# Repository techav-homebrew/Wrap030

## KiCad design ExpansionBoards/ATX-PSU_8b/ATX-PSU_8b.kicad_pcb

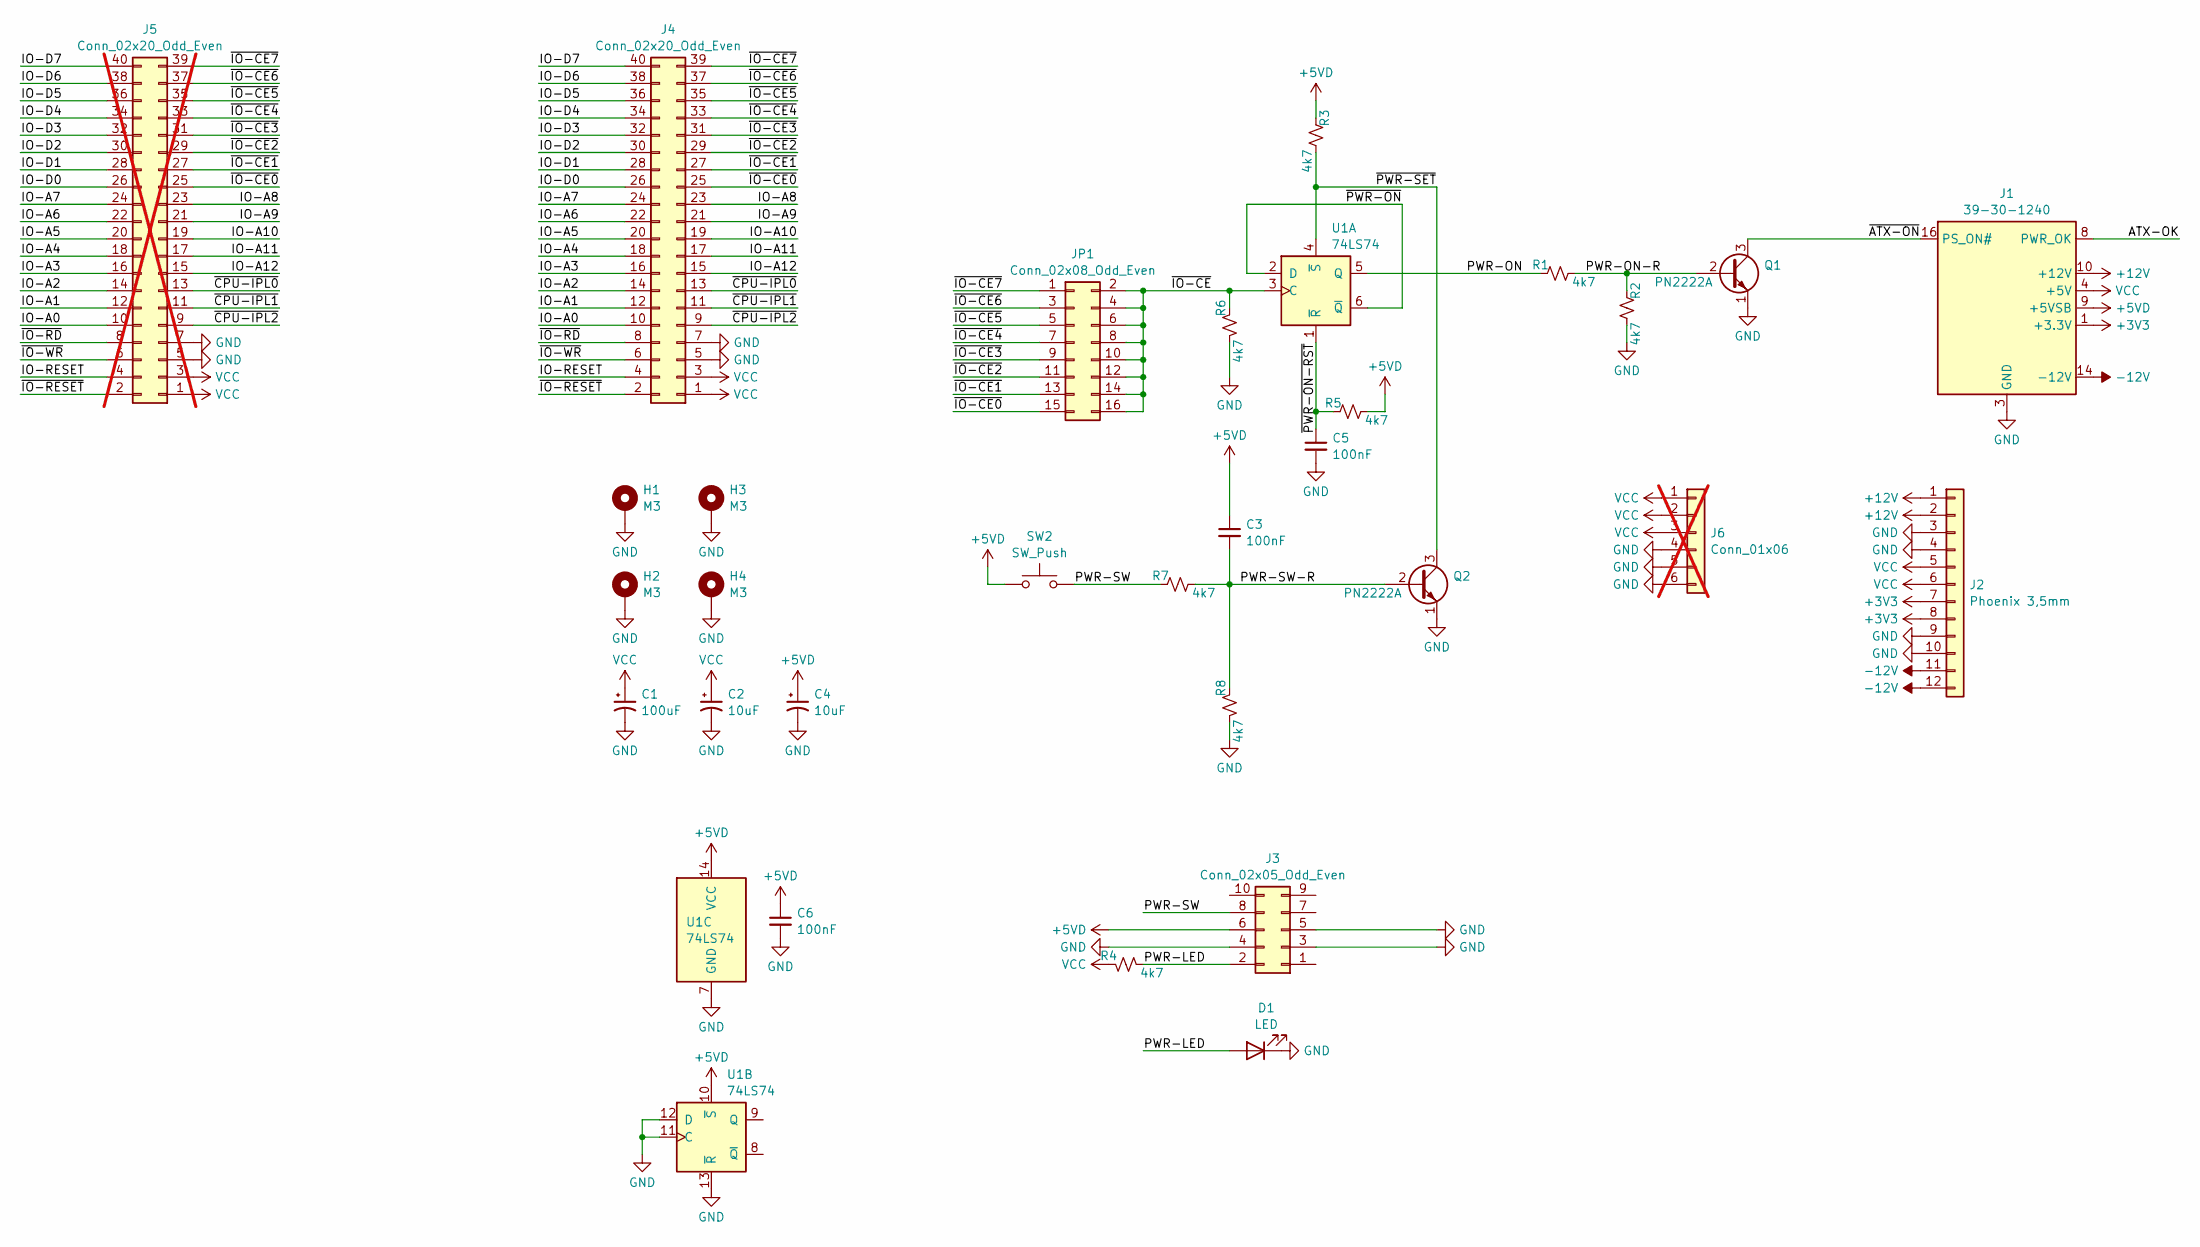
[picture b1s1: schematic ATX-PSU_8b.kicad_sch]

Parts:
C1: 100uF; CP_Radial_D10.0mm_P5.00mm
C2, C4: 10uF; CP_Radial_D5.0mm_P2.50mm
C3, C5, C6: 100nF; C_Disc_D4.3mm_W1.9mm_P5.00mm
D1: LED; LED_D3.0mm
H1, H2, H3, H4: M3; MountingHole_3.2mm_M3_Pad_Via
J1: 39-30-1240; Molex_Mini-Fit_Jr_5569-24A2_2x12_P4.20mm_Horizontal; Mouser 538-39-30-1240
J2: Phoenix 3,5mm; PhoenixContact_MC_1,5_12-G-3.5_1x12_P3.50mm_Horizontal
J3: Conn_02x05_Odd_Even; IDC-Header_2x05_P2.54mm_Vertical
J4: Conn_02x20_Odd_Even; PinHeader_2x20_P2.54mm_Horizontal
J5: Conn_02x20_Odd_Even; PinHeader_2x20_P2.54mm_Vertical; not fitted
J6: Conn_01x06; PinHeader_1x06_P2.54mm_Vertical; not fitted
JP1: Conn_02x08_Odd_Even; PinHeader_2x08_P2.54mm_Vertical
Q1, Q2: PN2222A; TO-92_Inline
R1, R2, R3, R4, R5, R6, R7, R8: 4k7; R_Axial_DIN0204_L3.6mm_D1.6mm_P7.62mm_Horizontal
SW2: SW_Push; SW_PUSH_6mm_H4.3mm
U1: 74LS74; DIP-14_W7.62mm

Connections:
+3V3: J1.1 (+3.3V), J1.2 (+3.3V), J1.12 (+3.3V), J1.13 (+3.3V), J2.7, J2.8
+5VD: C3.1, C4.1, C6.1, J1.9 (+5VSB), J3.6, R3.1, R5.2, SW2.1, U1.10 (~S), U1.14 (VCC)
+12V: J1.10 (+12V), J1.11 (+12V), J2.1, J2.2
-12V: J1.14 (-12V), J2.11, J2.12
/ATX-OK: J1.8 (PWR_OK)
/IO-A0: J4.10, J5.10
/IO-A1: J4.12, J5.12
/IO-A2: J4.14, J5.14
/IO-A3: J4.16, J5.16
/IO-A4: J4.18, J5.18
/IO-A5: J4.20, J5.20
/IO-A6: J4.22, J5.22
/IO-A7: J4.24, J5.24
/IO-A8: J4.23, J5.23
/IO-A9: J4.21, J5.21
/IO-A10: J4.19, J5.19
/IO-A11: J4.17, J5.17
/IO-A12: J4.15, J5.15
/IO-D0: J4.26, J5.26
/IO-D1: J4.28, J5.28
/IO-D2: J4.30, J5.30
/IO-D3: J4.32, J5.32
/IO-D4: J4.34, J5.34
/IO-D5: J4.36, J5.36
/IO-D6: J4.38, J5.38
/IO-D7: J4.40, J5.40
/IO-RESET: J4.4, J5.4
/PWR-LED: D1.2 (A), J3.2, R4.1
/PWR-ON: R1.1, U1.5 (Q)
/PWR-ON-R: Q1.2 (B), R1.2, R2.1
/PWR-SW: J3.8, R7.1, SW2.2
/PWR-SW-R: C3.2, Q2.2 (B), R7.2, R8.1
/~ATX-ON: J1.16 (PS_ON#), Q1.3 (C)
/~CPU-IPL0: J4.13, J5.13
/~CPU-IPL1: J4.11, J5.11
/~CPU-IPL2: J4.9, J5.9
/~IO-CE0: J4.25, J5.25, JP1.15
/~IO-CE1: J4.27, J5.27, JP1.13
/~IO-CE2: J4.29, J5.29, JP1.11
/~IO-CE3: J4.31, J5.31, JP1.9
/~IO-CE4: J4.33, J5.33, JP1.7
/~IO-CE5: J4.35, J5.35, JP1.5
/~IO-CE6: J4.37, J5.37, JP1.3
/~IO-CE7: J4.39, J5.39, JP1.1
/~IO-CE: JP1.2, JP1.4, JP1.6, JP1.8, JP1.10, JP1.12, JP1.14, JP1.16, R6.1, U1.3 (C)
/~IO-RD: J4.8, J5.8
/~IO-RESET: J4.2, J5.2
/~IO-WR: J4.6, J5.6
/~PWR-ON-RST: C5.1, R5.1, U1.1 (~R)
/~PWR-ON: U1.2 (D), U1.6 (~Q)
/~PWR-SET: Q2.3 (C), R3.2, U1.4 (~S)
GND: C1.2, C2.2, C4.2, C5.2, C6.2, D1.1 (K), H1.1, H2.1, H3.1, H4.1, J1.3 (GND), J1.5 (GND), J1.7 (GND), J1.15 (GND), J1.17 (GND), J1.18 (GND), J1.19 (GND), J1.24 (GND), J2.3, J2.4, J2.9, J2.10, J3.3, J3.4, J3.5, J4.5, J4.7, J5.5, J5.7, J6.4, J6.5, J6.6, Q1.1 (E), Q2.1 (E), R2.2, R6.2, R8.2, U1.7 (GND), U1.11 (C), U1.12 (D), U1.13 (~R)
VCC: C1.1, C2.1, J1.4 (+5V), J1.6 (+5V), J1.21 (+5V), J1.22 (+5V), J1.23 (+5V), J2.5, J2.6, J4.1, J4.3, J5.1, J5.3, J6.1, J6.2, J6.3, R4.2

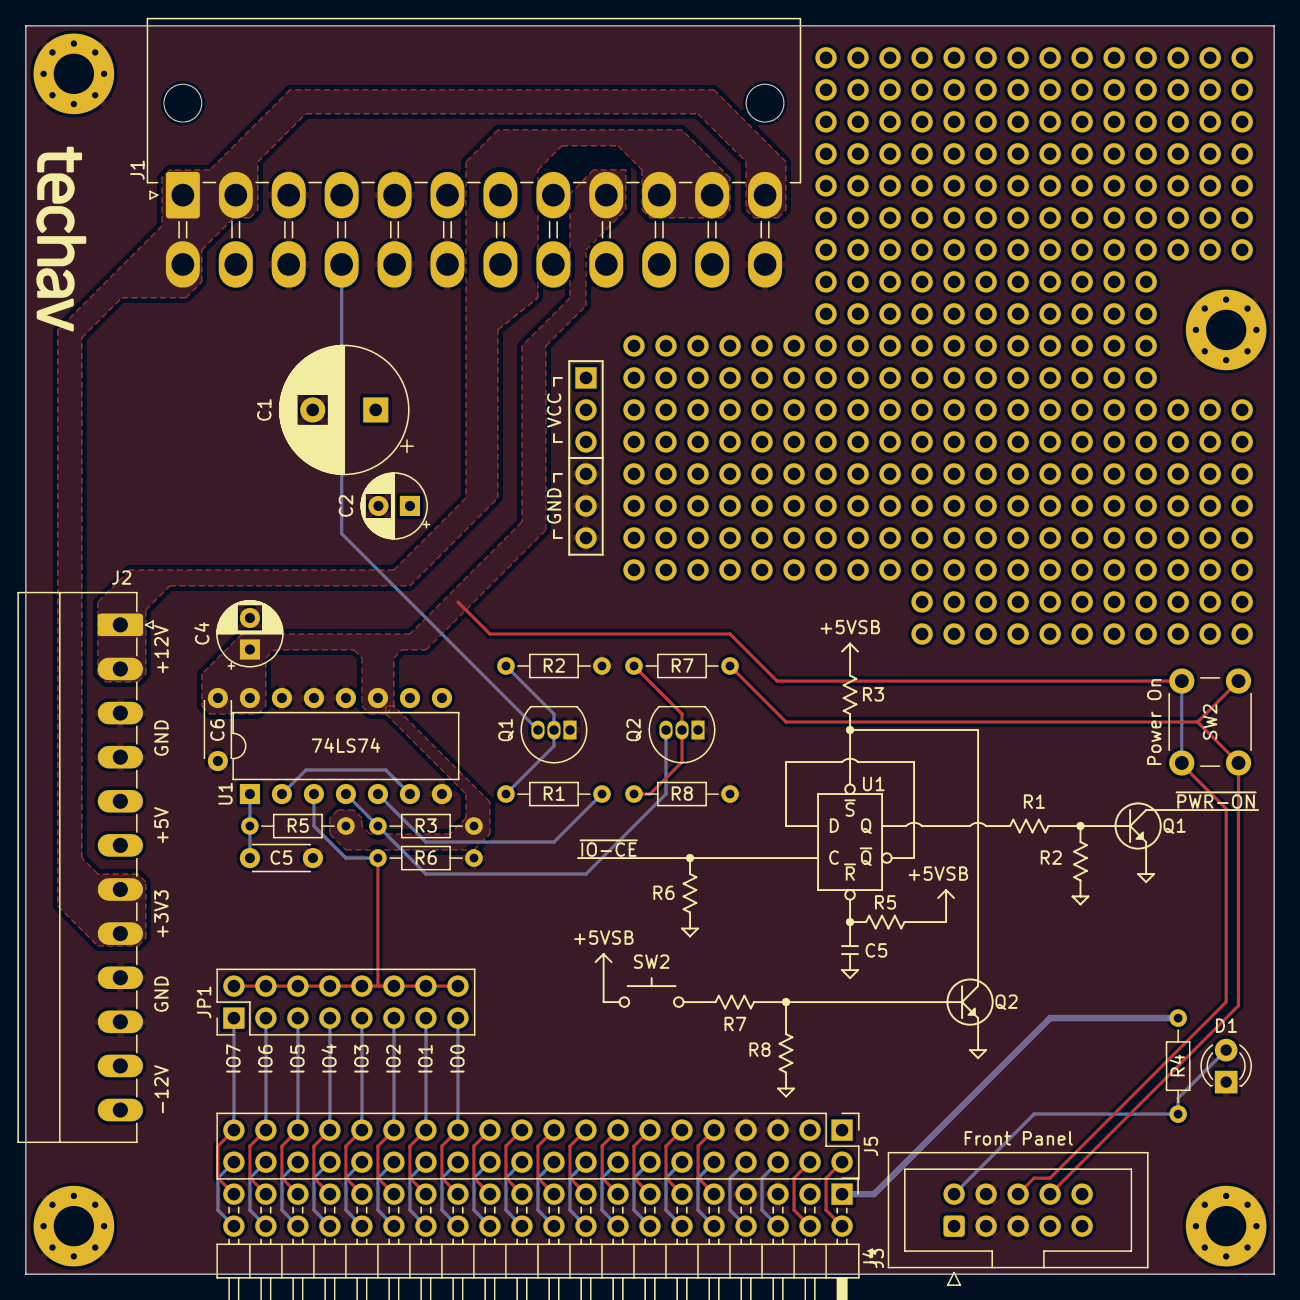
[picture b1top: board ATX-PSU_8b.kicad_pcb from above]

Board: 2 copper layers, 99.1 x 99.1 mm, 29 parts (0 on the bottom side), 52 nets.

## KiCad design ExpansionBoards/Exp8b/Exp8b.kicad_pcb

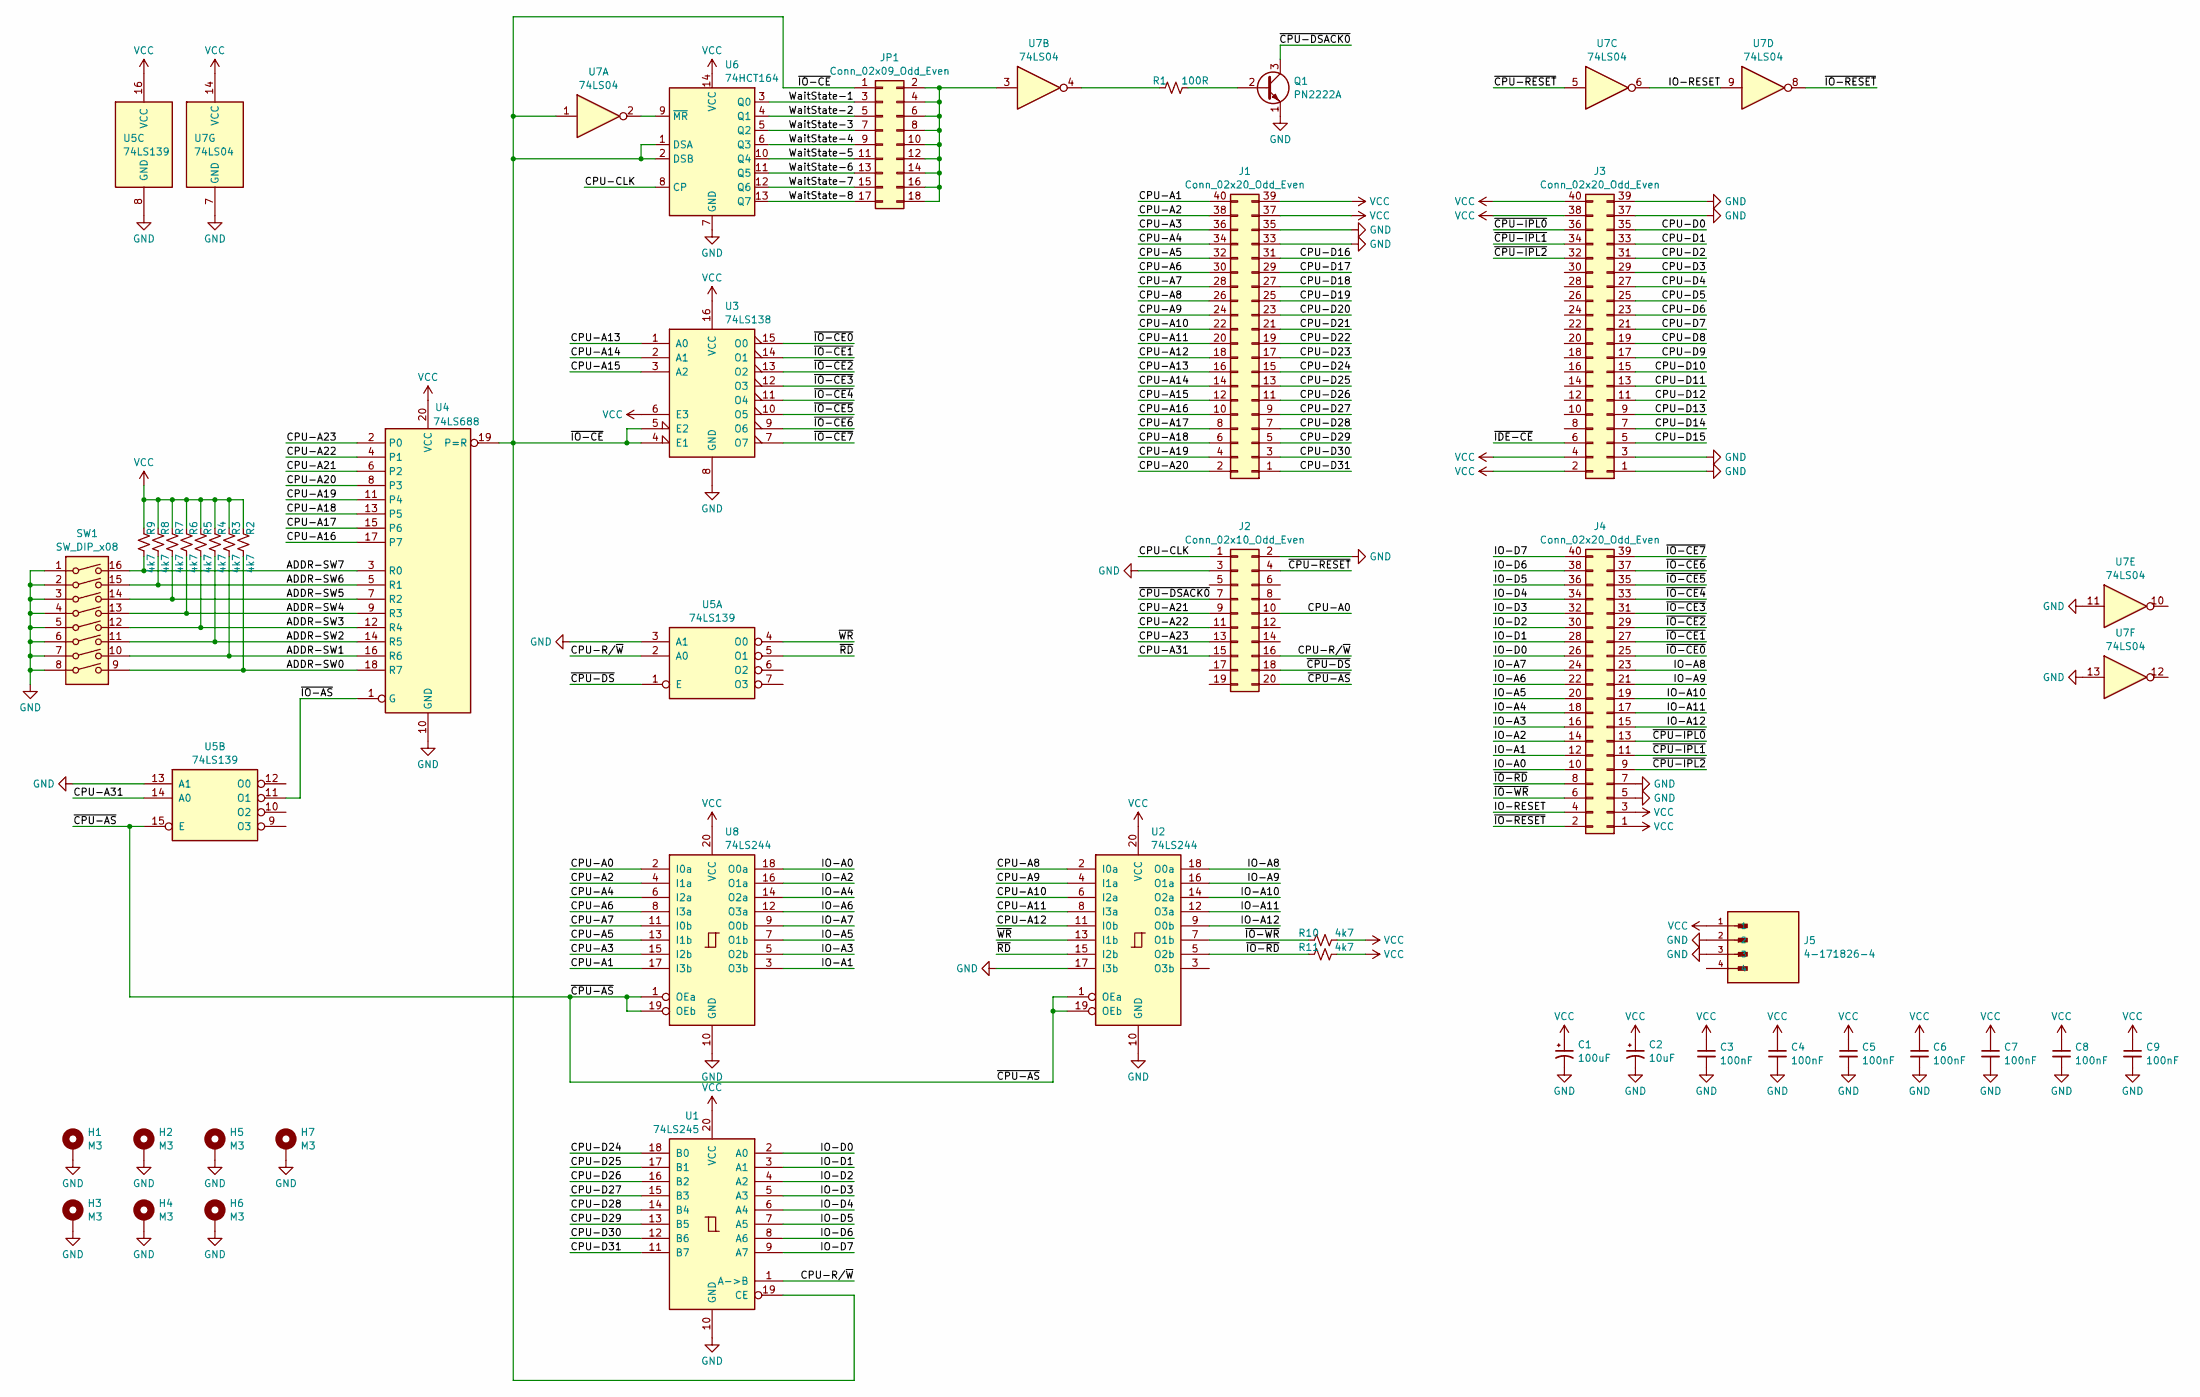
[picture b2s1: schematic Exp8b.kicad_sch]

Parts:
C1: 100uF; CP_Radial_D10.0mm_P5.00mm
C2: 10uF; CP_Radial_D5.0mm_P2.50mm
C3, C4, C5, C6, C7, C8, C9: 100nF; C_Disc_D4.3mm_W1.9mm_P5.00mm
H1, H2, H3, H4, H5, H6, H7: M3; MountingHole_3.2mm_M3_Pad_Via
J1, J3, J4: Conn_02x20_Odd_Even; PinHeader_2x20_P2.54mm_Horizontal
J2: Conn_02x10_Odd_Even; PinHeader_2x10_P2.54mm_Horizontal
J5: 4-171826-4; TE_4-171826-4
JP1: Conn_02x09_Odd_Even; PinHeader_2x09_P2.54mm_Vertical
Q1: PN2222A; TO-92_Inline
R1: 100R; R_Axial_DIN0204_L3.6mm_D1.6mm_P7.62mm_Horizontal
R2, R3, R4, R5, R6, R7, R8, R9, R10, R11: 4k7; R_Axial_DIN0204_L3.6mm_D1.6mm_P7.62mm_Horizontal
SW1: SW_DIP_x08; SW_DIP_SPSTx08_Slide_9.78x22.5mm_W7.62mm_P2.54mm
U1: 74LS245; DIP-20_W7.62mm_Socket
U2, U8: 74LS244; DIP-20_W7.62mm_Socket
U3: 74LS138; DIP-16_W7.62mm_Socket
U4: 74LS688; DIP-20_W7.62mm_Socket
U5: 74LS139; DIP-16_W7.62mm_Socket
U6: 74HCT164; DIP-14_W7.62mm_Socket
U7: 74LS04; DIP-14_W7.62mm_Socket

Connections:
/ADDR-SW0: R2.2, SW1.9, U4.18 (R7)
/ADDR-SW1: R3.2, SW1.10, U4.16 (R6)
/ADDR-SW2: R4.2, SW1.11, U4.14 (R5)
/ADDR-SW3: R5.2, SW1.12, U4.12 (R4)
/ADDR-SW4: R6.2, SW1.13, U4.9 (R3)
/ADDR-SW5: R7.2, SW1.14, U4.7 (R2)
/ADDR-SW6: R8.2, SW1.15, U4.5 (R1)
/ADDR-SW7: R9.2, SW1.16, U4.3 (R0)
/CPU-A0: J2.10, U8.2 (I0a)
/CPU-A1: J1.40, U8.17 (I3b)
/CPU-A2: J1.38, U8.4 (I1a)
/CPU-A3: J1.36, U8.15 (I2b)
/CPU-A4: J1.34, U8.6 (I2a)
/CPU-A5: J1.32, U8.13 (I1b)
/CPU-A6: J1.30, U8.8 (I3a)
/CPU-A7: J1.28, U8.11 (I0b)
/CPU-A8: J1.26, U2.2 (I0a)
/CPU-A9: J1.24, U2.4 (I1a)
/CPU-A10: J1.22, U2.6 (I2a)
/CPU-A11: J1.20, U2.8 (I3a)
/CPU-A12: J1.18, U2.11 (I0b)
/CPU-A13: J1.16, U3.1 (A0)
/CPU-A14: J1.14, U3.2 (A1)
/CPU-A15: J1.12, U3.3 (A2)
/CPU-A16: J1.10, U4.17 (P7)
/CPU-A17: J1.8, U4.15 (P6)
/CPU-A18: J1.6, U4.13 (P5)
/CPU-A19: J1.4, U4.11 (P4)
/CPU-A20: J1.2, U4.8 (P3)
/CPU-A21: J2.9, U4.6 (P2)
/CPU-A22: J2.11, U4.4 (P1)
/CPU-A23: J2.13, U4.2 (P0)
/CPU-A31: J2.15, U5.14 (A0)
/CPU-CLK: J2.1, U6.8 (CP)
/CPU-D0: J3.35
/CPU-D1: J3.33
/CPU-D2: J3.31
/CPU-D3: J3.29
/CPU-D4: J3.27
/CPU-D5: J3.25
/CPU-D6: J3.23
/CPU-D7: J3.21
/CPU-D8: J3.19
/CPU-D9: J3.17
/CPU-D10: J3.15
/CPU-D11: J3.13
/CPU-D12: J3.11
/CPU-D13: J3.9
/CPU-D14: J3.7
/CPU-D15: J3.5
/CPU-D16: J1.31
/CPU-D17: J1.29
/CPU-D18: J1.27
/CPU-D19: J1.25
/CPU-D20: J1.23
/CPU-D21: J1.21
/CPU-D22: J1.19
/CPU-D23: J1.17
/CPU-D24: J1.15, U1.18 (B0)
/CPU-D25: J1.13, U1.17 (B1)
/CPU-D26: J1.11, U1.16 (B2)
/CPU-D27: J1.9, U1.15 (B3)
/CPU-D28: J1.7, U1.14 (B4)
/CPU-D29: J1.5, U1.13 (B5)
/CPU-D30: J1.3, U1.12 (B6)
/CPU-D31: J1.1, U1.11 (B7)
/CPU-R/~W: J2.16, U1.1 (A->B), U5.2 (A0)
/IO-A0: J4.10, U8.18 (O0a)
/IO-A1: J4.12, U8.3 (O3b)
/IO-A2: J4.14, U8.16 (O1a)
/IO-A3: J4.16, U8.5 (O2b)
/IO-A4: J4.18, U8.14 (O2a)
/IO-A5: J4.20, U8.7 (O1b)
/IO-A6: J4.22, U8.12 (O3a)
/IO-A7: J4.24, U8.9 (O0b)
/IO-A8: J4.23, U2.18 (O0a)
/IO-A9: J4.21, U2.16 (O1a)
/IO-A10: J4.19, U2.14 (O2a)
/IO-A11: J4.17, U2.12 (O3a)
/IO-A12: J4.15, U2.9 (O0b)
/IO-D0: J4.26, U1.2 (A0)
/IO-D1: J4.28, U1.3 (A1)
/IO-D2: J4.30, U1.4 (A2)
/IO-D3: J4.32, U1.5 (A3)
/IO-D4: J4.34, U1.6 (A4)
/IO-D5: J4.36, U1.7 (A5)
/IO-D6: J4.38, U1.8 (A6)
/IO-D7: J4.40, U1.9 (A7)
/IO-RESET: J4.4, U7.6, U7.9
/WaitState-1: JP1.3, U6.3 (Q0)
/WaitState-2: JP1.5, U6.4 (Q1)
/WaitState-3: JP1.7, U6.5 (Q2)
/WaitState-4: JP1.9, U6.6 (Q3)
/WaitState-5: JP1.11, U6.10 (Q4)
/WaitState-6: JP1.13, U6.11 (Q5)
/WaitState-7: JP1.15, U6.12 (Q6)
/WaitState-8: JP1.17, U6.13 (Q7)
/~CPU-AS: J2.20, U2.1 (OEa), U2.19 (OEb), U5.15 (E), U8.1 (OEa), U8.19 (OEb)
/~CPU-DSACK0: J2.7, Q1.3 (C)
/~CPU-DS: J2.18, U5.1 (E)
/~CPU-IPL0: J3.36, J4.13
/~CPU-IPL1: J3.34, J4.11
/~CPU-IPL2: J3.32, J4.9
/~CPU-RESET: J2.4, U7.5
/~IDE-CE: J3.6
/~IO-AS: U4.1 (G), U5.11 (O1)
/~IO-CE0: J4.25, U3.15 (O0)
/~IO-CE1: J4.27, U3.14 (O1)
/~IO-CE2: J4.29, U3.13 (O2)
/~IO-CE3: J4.31, U3.12 (O3)
/~IO-CE4: J4.33, U3.11 (O4)
/~IO-CE5: J4.35, U3.10 (O5)
/~IO-CE6: J4.37, U3.9 (O6)
/~IO-CE7: J4.39, U3.7 (O7)
/~IO-CE: JP1.1, U1.19 (CE), U3.4 (E1), U3.5 (E2), U4.19 (P=R), U6.1 (DSA), U6.2 (DSB), U7.1
/~IO-RD: J4.8, R11.1, U2.5 (O2b)
/~IO-RESET: J4.2, U7.8
/~IO-WR: J4.6, R10.1, U2.7 (O1b)
/~RD: U2.15 (I2b), U5.5 (O1)
/~WR: U2.13 (I1b), U5.4 (O0)
GND: C1.2, C2.2, C3.2, C4.2, C5.2, C6.2, C7.2, C8.2, C9.2, H1.1, H2.1, H3.1, H4.1, H5.1, H6.1, H7.1, J1.33, J1.35, J2.2, J2.3, J3.1, J3.3, J3.37, J3.39, J4.5, J4.7, J5.2, J5.3, Q1.1 (E), SW1.1, SW1.2, SW1.3, SW1.4, SW1.5, SW1.6, SW1.7, SW1.8, U1.10 (GND), U2.10 (GND), U2.17 (I3b), U3.8 (GND), U4.10 (GND), U5.3 (A1), U5.8 (GND), U5.13 (A1), U6.7 (GND), U7.7 (GND), U7.11, U7.13, U8.10 (GND)
unnamed: JP1.2, JP1.4, JP1.6, JP1.8, JP1.10, JP1.12, JP1.14, JP1.16, JP1.18, U7.3
unnamed: Q1.2 (B), R1.2
unnamed: R1.1, U7.4
unnamed: U6.9 (~MR), U7.2
VCC: C1.1, C2.1, C3.1, C4.1, C5.1, C6.1, C7.1, C8.1, C9.1, J1.37, J1.39, J3.2, J3.4, J3.38, J3.40, J4.1, J4.3, J5.1, R2.1, R3.1, R4.1, R5.1, R6.1, R7.1, R8.1, R9.1, R10.2, R11.2, U1.20 (VCC), U2.20 (VCC), U3.6 (E3), U3.16 (VCC), U4.20 (VCC), U5.16 (VCC), U6.14 (VCC), U7.14 (VCC), U8.20 (VCC)

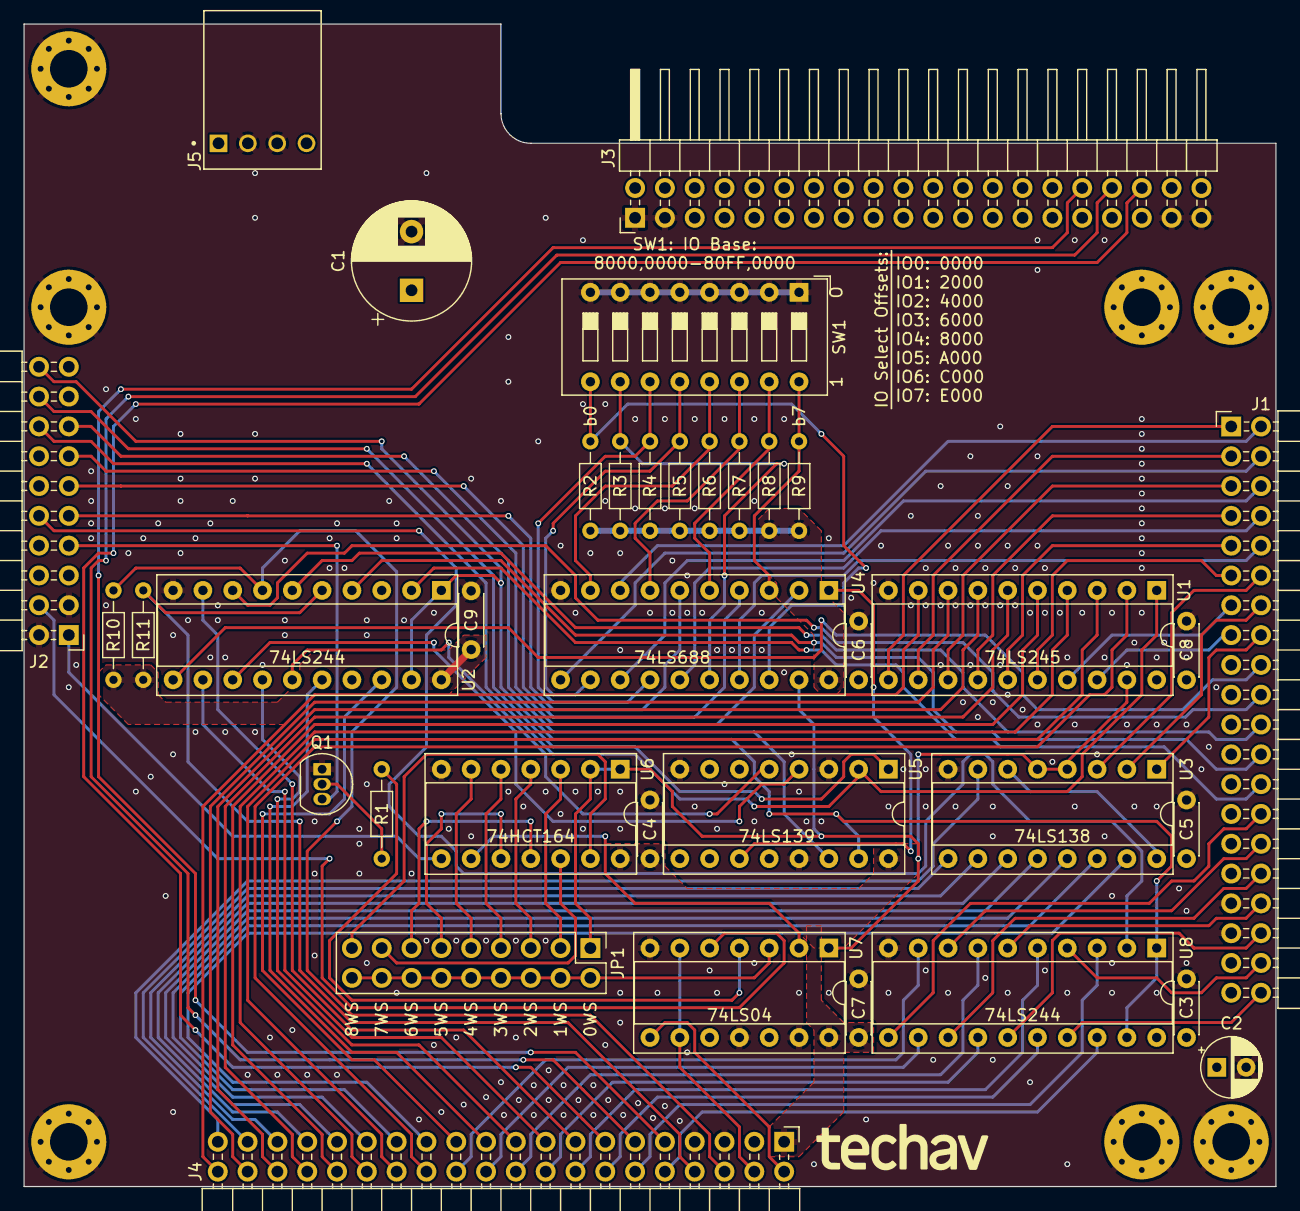
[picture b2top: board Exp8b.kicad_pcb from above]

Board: 2 copper layers, 106.7 x 99.1 mm, 43 parts (0 on the bottom side), 101 nets.

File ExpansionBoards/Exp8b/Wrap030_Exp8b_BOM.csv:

"Reference","Value","Datasheet","Footprint","Qty","DNP"
"C1","100uF","~","Capacitor_THT:CP_Radial_D10.0mm_P5.00mm","1",""
"C2","10uF","~","Capacitor_THT:CP_Radial_D5.0mm_P2.50mm","1",""
"C3,C4,C5,C6,C7,C8,C9","100nF","~","Capacitor_THT:C_Disc_D4.3mm_W1.9mm_P5.00mm","7",""
"J1,J3,J4","Conn_02x20_Odd_Even","~","Connector_PinHeader_2.54mm:PinHeader_2x20_P2.54mm_Horizontal","3",""
"J2","Conn_02x10_Odd_Even","~","Connector_PinHeader_2.54mm:PinHeader_2x10_P2.54mm_Horizontal","1",""
"J5","4-171826-4","","Exp8b:TE_4-171826-4","1",""
"JP1","Conn_02x09_Odd_Even","~","Connector_PinHeader_2.54mm:PinHeader_2x09_P2.54mm_Vertical","1",""
"Q1","PN2222A","https://www.onsemi.com/pub/Collateral/PN2222-D.PDF","Package_TO_SOT_THT:TO-92_Inline","1",""
"R1","100R","~","Resistor_THT:R_Axial_DIN0204_L3.6mm_D1.6mm_P7.62mm_Horizontal","1",""
"R2,R3,R4,R5,R6,R7,R8,R9,R10,R11","4k7","~","Resistor_THT:R_Axial_DIN0204_L3.6mm_D1.6mm_P7.62mm_Horizontal","10",""
"SW1","SW_DIP_x08","~","Button_Switch_THT:SW_DIP_SPSTx08_Slide_9.78x22.5mm_W7.62mm_P2.54mm","1",""
"U1","74LS245","http://www.ti.com/lit/gpn/sn74LS245","Package_DIP:DIP-20_W7.62mm_Socket","1",""
"U2,U8","74LS244","http://www.ti.com/lit/ds/symlink/sn74ls244.pdf","Package_DIP:DIP-20_W7.62mm_Socket","2",""
"U3","74LS138","http://www.ti.com/lit/gpn/sn74LS138","Package_DIP:DIP-16_W7.62mm_Socket","1",""
"U4","74LS688","http://www.ti.com/lit/gpn/sn74LS688","Package_DIP:DIP-20_W7.62mm_Socket","1",""
"U5","74LS139","http://www.ti.com/lit/ds/symlink/sn74ls139a.pdf","Package_DIP:DIP-16_W7.62mm_Socket","1",""
"U6","74HCT164","https://assets.nexperia.com/documents/data-sheet/74HC_HCT164.pdf","Package_DIP:DIP-14_W7.62mm_Socket","1",""
"U7","74LS04","http://www.ti.com/lit/gpn/sn74LS04","Package_DIP:DIP-14_W7.62mm_Socket","1",""

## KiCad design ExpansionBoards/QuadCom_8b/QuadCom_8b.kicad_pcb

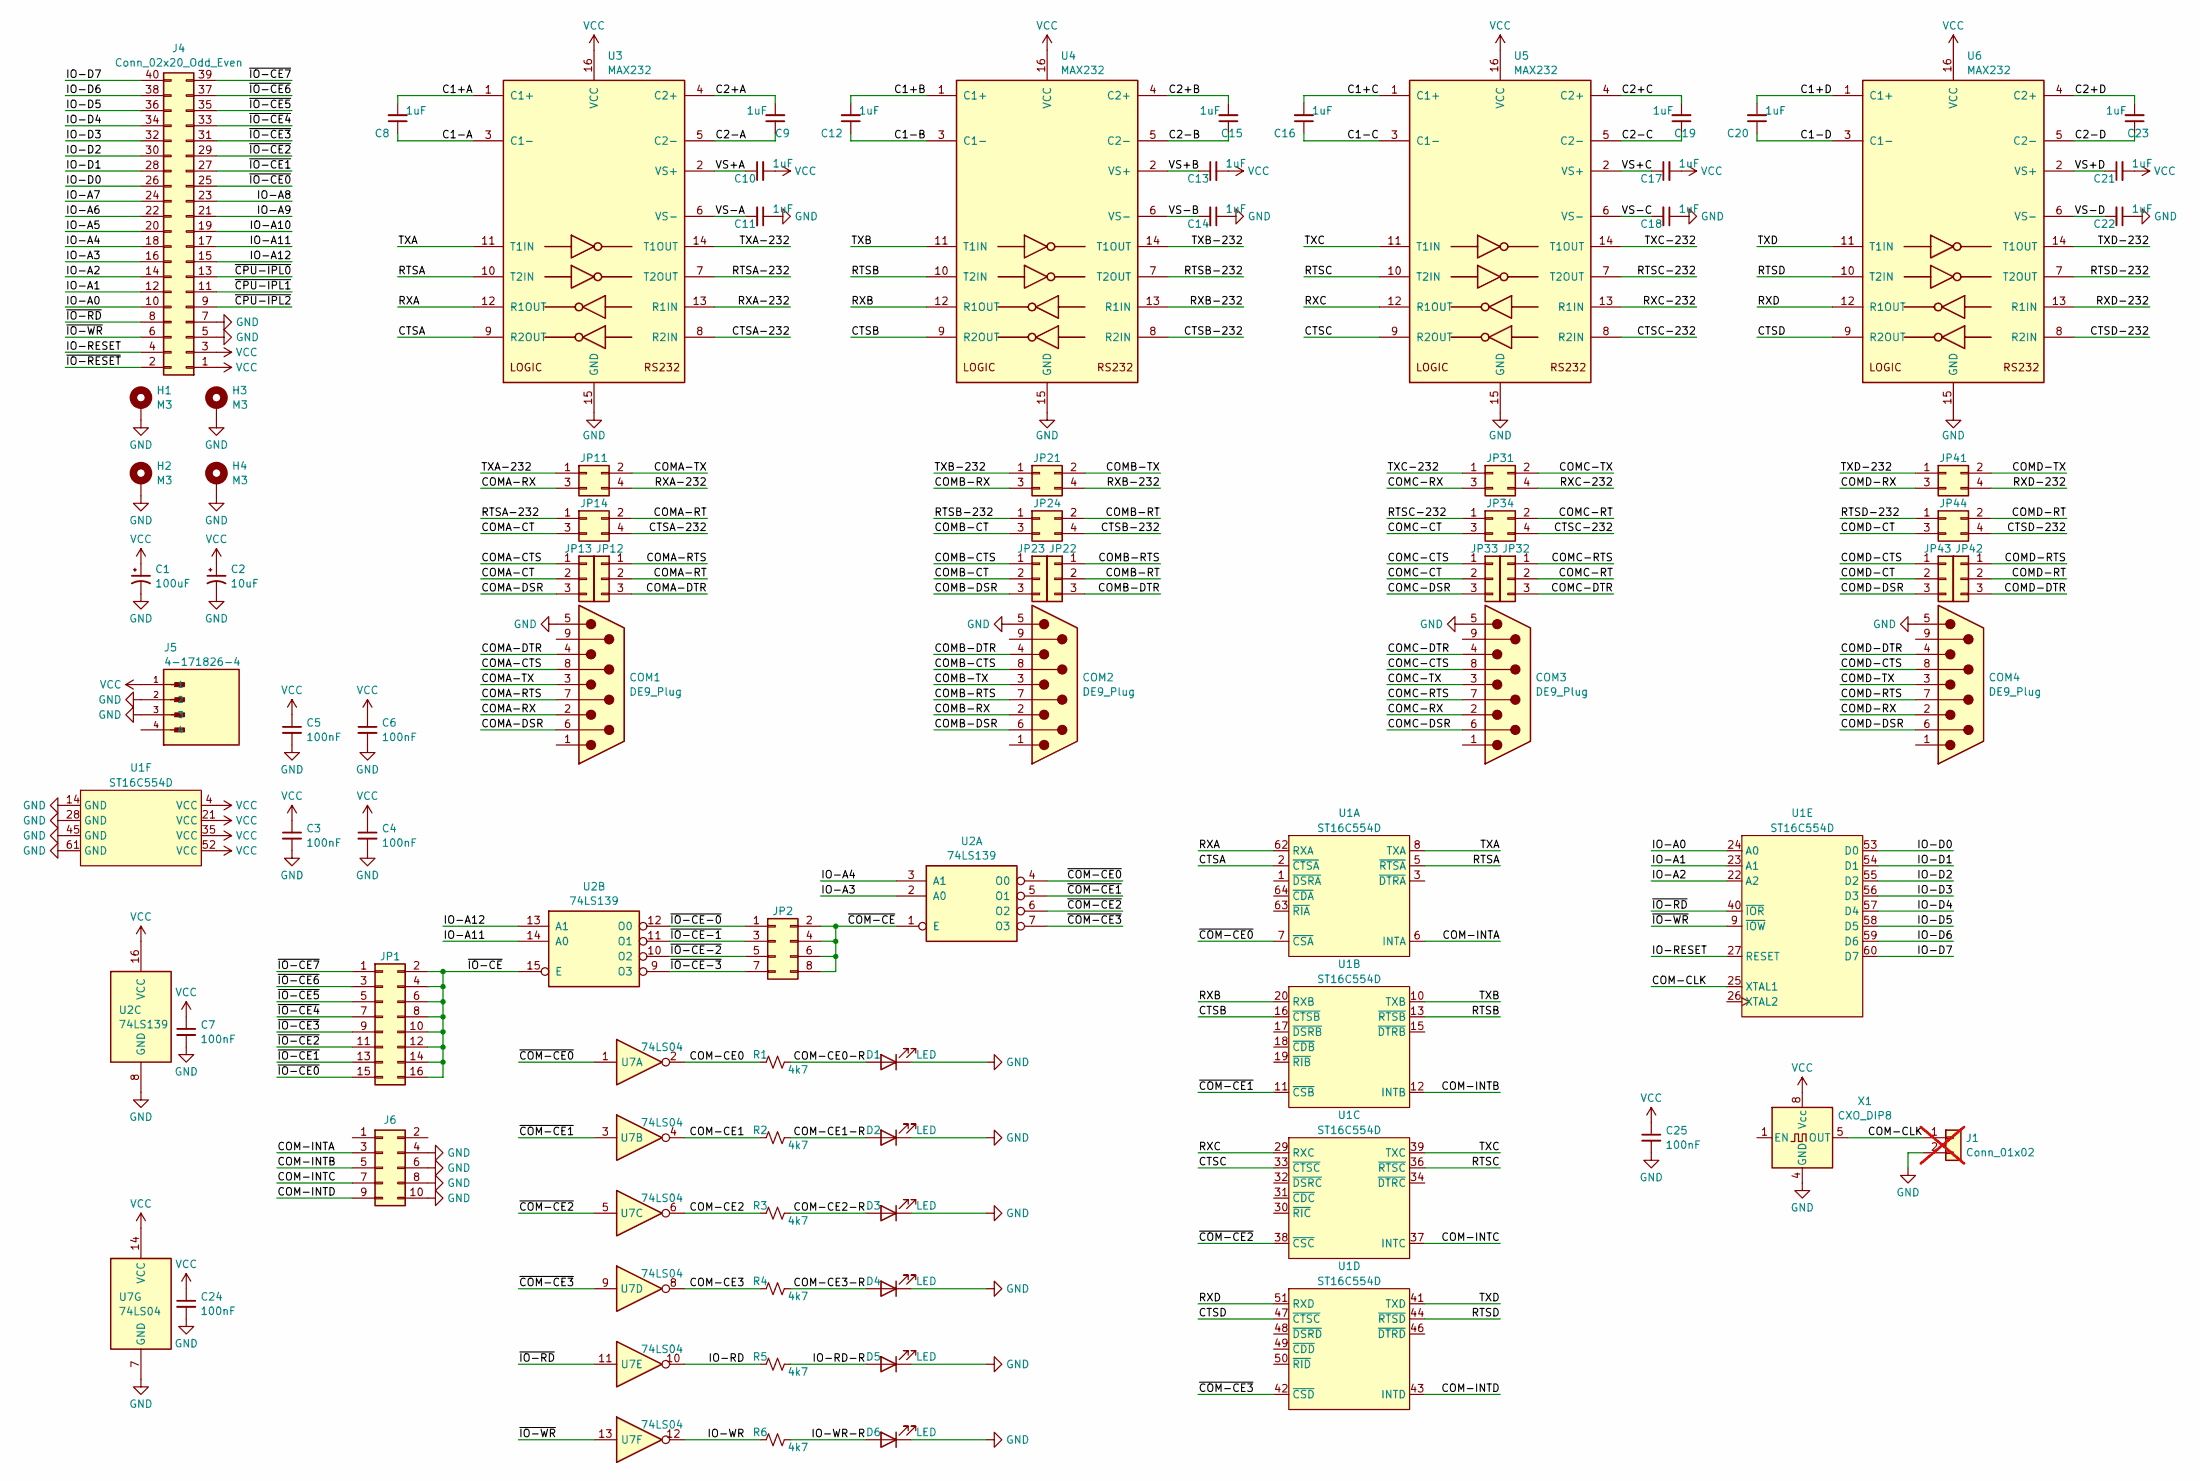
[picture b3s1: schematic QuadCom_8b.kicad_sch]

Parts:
C1: 100uF; CP_Radial_D10.0mm_P5.00mm
C2: 10uF; CP_Radial_D5.0mm_P2.50mm
C3, C4, C5, C6, C7, C24, C25: 100nF; C_Disc_D4.3mm_W1.9mm_P5.00mm
C8, C9, C10, C11, C12, C13, C14, C15, C16, C17, C18, C19, C20, C21, C22, C23: 1uF; C_Disc_D4.3mm_W1.9mm_P5.00mm
COM1, COM2, COM3, COM4: DE9_Plug; DSUB-9_Male_EdgeMount_P2.77mm
D1, D2, D3, D4, D5, D6: LED; LED_D3.0mm_Horizontal_O1.27mm_Z2.0mm
H1, H2, H3, H4: M3; MountingHole_3.2mm_M3_Pad_Via
J1: Conn_01x02; PinHeader_1x02_P2.54mm_Vertical; not fitted
J4: Conn_02x20_Odd_Even; PinHeader_2x20_P2.54mm_Horizontal
J5: 4-171826-4; TE_4-171826-4
J6: Conn_02x05_Odd_Even; IDC-Header_2x05_P2.54mm_Vertical
JP1: Conn_02x08_Odd_Even; PinHeader_2x08_P2.54mm_Vertical
JP2: Conn_02x04_Odd_Even; PinHeader_2x04_P2.54mm_Vertical
JP11, JP14, JP21, JP24, JP31, JP34, JP41, JP44: Conn_02x02_Odd_Even; PinHeader_2x02_P2.54mm_Vertical
JP12, JP13, JP22, JP23, JP32, JP33, JP42, JP43: Conn_01x03; PinHeader_1x03_P2.54mm_Vertical
R1, R2, R3, R4, R5, R6: 4k7; R_Axial_DIN0204_L3.6mm_D1.6mm_P7.62mm_Horizontal
U1: ST16C554D; LQFP-64_10x10mm_P0.5mm; Mouser 701-ST16C554DIQ64-F
U2: 74LS139; DIP-16_W7.62mm
U3, U4, U5, U6: MAX232; DIP-16_W7.62mm
U7: 74LS04; DIP-14_W7.62mm
X1: CXO_DIP8; Oscillator_DIP-8

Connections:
/C1+A: C8.2, U3.1 (C1+)
/C1+B: C12.2, U4.1 (C1+)
/C1+C: C16.2, U5.1 (C1+)
/C1+D: C20.2, U6.1 (C1+)
/C1-A: C8.1, U3.3 (C1-)
/C1-B: C12.1, U4.3 (C1-)
/C1-C: C16.1, U5.3 (C1-)
/C1-D: C20.1, U6.3 (C1-)
/C2+A: C9.2, U3.4 (C2+)
/C2+B: C15.2, U4.4 (C2+)
/C2+C: C19.2, U5.4 (C2+)
/C2+D: C23.2, U6.4 (C2+)
/C2-A: C9.1, U3.5 (C2-)
/C2-B: C15.1, U4.5 (C2-)
/C2-C: C19.1, U5.5 (C2-)
/C2-D: C23.1, U6.5 (C2-)
/COM-CE0: R1.1, U7.2
/COM-CE0-R: D1.2 (A), R1.2
/COM-CE1: R2.1, U7.4
/COM-CE1-R: D2.2 (A), R2.2
/COM-CE2: R3.1, U7.6
/COM-CE2-R: D3.2 (A), R3.2
/COM-CE3: R4.1, U7.8
/COM-CE3-R: D4.2 (A), R4.2
/COM-CLK: J1.1, U1.25 (XTAL1), X1.5 (OUT)
/COM-INTA: J6.3, U1.6 (INTA)
/COM-INTB: J6.5, U1.12 (INTB)
/COM-INTC: J6.7, U1.37 (INTC)
/COM-INTD: J6.9, U1.43 (INTD)
/COMA-CT: JP13.2, JP14.3
/COMA-CTS: COM1.8, JP13.1
/COMA-DSR: COM1.6, JP13.3
/COMA-DTR: COM1.4, JP12.3
/COMA-RT: JP12.2, JP14.2
/COMA-RTS: COM1.7, JP12.1
/COMA-RX: COM1.2, JP11.3
/COMA-TX: COM1.3, JP11.2
/COMB-CT: JP23.2, JP24.3
/COMB-CTS: COM2.8, JP23.1
/COMB-DSR: COM2.6, JP23.3
/COMB-DTR: COM2.4, JP22.3
/COMB-RT: JP22.2, JP24.2
/COMB-RTS: COM2.7, JP22.1
/COMB-RX: COM2.2, JP21.3
/COMB-TX: COM2.3, JP21.2
/COMC-CT: JP33.2, JP34.3
/COMC-CTS: COM3.8, JP33.1
/COMC-DSR: COM3.6, JP33.3
/COMC-DTR: COM3.4, JP32.3
/COMC-RT: JP32.2, JP34.2
/COMC-RTS: COM3.7, JP32.1
/COMC-RX: COM3.2, JP31.3
/COMC-TX: COM3.3, JP31.2
/COMD-CT: JP43.2, JP44.3
/COMD-CTS: COM4.8, JP43.1
/COMD-DSR: COM4.6, JP43.3
/COMD-DTR: COM4.4, JP42.3
/COMD-RT: JP42.2, JP44.2
/COMD-RTS: COM4.7, JP42.1
/COMD-RX: COM4.2, JP41.3
/COMD-TX: COM4.3, JP41.2
/CTSA: U1.2 (~CTSA), U3.9 (R2OUT)
/CTSA-232: JP14.4, U3.8 (R2IN)
/CTSB: U1.16 (~CTSB), U4.9 (R2OUT)
/CTSB-232: JP24.4, U4.8 (R2IN)
/CTSC: U1.33 (~CTSC), U5.9 (R2OUT)
/CTSC-232: JP34.4, U5.8 (R2IN)
/CTSD: U1.47 (~CTSC), U6.9 (R2OUT)
/CTSD-232: JP44.4, U6.8 (R2IN)
/IO-A0: J4.10, U1.24 (A0)
/IO-A1: J4.12, U1.23 (A1)
/IO-A2: J4.14, U1.22 (A2)
/IO-A3: J4.16, U2.2 (A0)
/IO-A4: J4.18, U2.3 (A1)
/IO-A5: J4.20
/IO-A6: J4.22
/IO-A7: J4.24
/IO-A8: J4.23
/IO-A9: J4.21
/IO-A10: J4.19
/IO-A11: J4.17, U2.14 (A0)
/IO-A12: J4.15, U2.13 (A1)
/IO-D0: J4.26, U1.53 (D0)
/IO-D1: J4.28, U1.54 (D1)
/IO-D2: J4.30, U1.55 (D2)
/IO-D3: J4.32, U1.56 (D3)
/IO-D4: J4.34, U1.57 (D4)
/IO-D5: J4.36, U1.58 (D5)
/IO-D6: J4.38, U1.59 (D6)
/IO-D7: J4.40, U1.60 (D7)
/IO-RD: R5.1, U7.10
/IO-RD-R: D5.2 (A), R5.2
/IO-RESET: J4.4, U1.27 (RESET)
/IO-WR: R6.1, U7.12
/IO-WR-R: D6.2 (A), R6.2
/RTSA: U1.5 (~RTSA), U3.10 (T2IN)
/RTSA-232: JP14.1, U3.7 (T2OUT)
/RTSB: U1.13 (~RTSB), U4.10 (T2IN)
/RTSB-232: JP24.1, U4.7 (T2OUT)
/RTSC: U1.36 (~RTSC), U5.10 (T2IN)
/RTSC-232: JP34.1, U5.7 (T2OUT)
/RTSD: U1.44 (~RTSD), U6.10 (T2IN)
/RTSD-232: JP44.1, U6.7 (T2OUT)
/RXA: U1.62 (RXA), U3.12 (R1OUT)
/RXA-232: JP11.4, U3.13 (R1IN)
/RXB: U1.20 (RXB), U4.12 (R1OUT)
/RXB-232: JP21.4, U4.13 (R1IN)
/RXC: U1.29 (RXC), U5.12 (R1OUT)
/RXC-232: JP31.4, U5.13 (R1IN)
/RXD: U1.51 (RXD), U6.12 (R1OUT)
/RXD-232: JP41.4, U6.13 (R1IN)
/TXA: U1.8 (TXA), U3.11 (T1IN)
/TXA-232: JP11.1, U3.14 (T1OUT)
/TXB: U1.10 (TXB), U4.11 (T1IN)
/TXB-232: JP21.1, U4.14 (T1OUT)
/TXC: U1.39 (TXC), U5.11 (T1IN)
/TXC-232: JP31.1, U5.14 (T1OUT)
/TXD: U1.41 (TXD), U6.11 (T1IN)
/TXD-232: JP41.1, U6.14 (T1OUT)
/VS+A: C10.1, U3.2 (VS+)
/VS+B: C13.1, U4.2 (VS+)
/VS+C: C17.1, U5.2 (VS+)
/VS+D: C21.1, U6.2 (VS+)
/VS-A: C11.2, U3.6 (VS-)
/VS-B: C14.2, U4.6 (VS-)
/VS-C: C18.2, U5.6 (VS-)
/VS-D: C22.2, U6.6 (VS-)
/~COM-CE0: U1.7 (~CSA), U2.4 (O0), U7.1
/~COM-CE1: U1.11 (~CSB), U2.5 (O1), U7.3
/~COM-CE2: U1.38 (~CSC), U2.6 (O2), U7.5
/~COM-CE3: U1.42 (~CSD), U2.7 (O3), U7.9
/~COM-CE: JP2.2, JP2.4, JP2.6, JP2.8, U2.1 (E)
/~CPU-IPL0: J4.13
/~CPU-IPL1: J4.11
/~CPU-IPL2: J4.9
/~IO-CE0: J4.25, JP1.15
/~IO-CE1: J4.27, JP1.13
/~IO-CE2: J4.29, JP1.11
/~IO-CE3: J4.31, JP1.9
/~IO-CE4: J4.33, JP1.7
/~IO-CE5: J4.35, JP1.5
/~IO-CE6: J4.37, JP1.3
/~IO-CE7: J4.39, JP1.1
/~IO-CE-0: JP2.1, U2.12 (O0)
/~IO-CE-1: JP2.3, U2.11 (O1)
/~IO-CE-2: JP2.5, U2.10 (O2)
/~IO-CE-3: JP2.7, U2.9 (O3)
/~IO-CE: JP1.2, JP1.4, JP1.6, JP1.8, JP1.10, JP1.12, JP1.14, JP1.16, U2.15 (E)
/~IO-RD: J4.8, U1.40 (~IOR), U7.11
/~IO-RESET: J4.2
/~IO-WR: J4.6, U1.9 (~IOW), U7.13
GND: C1.2, C2.2, C3.2, C4.2, C5.2, C6.2, C7.2, C11.1, C14.1, C18.1, C22.1, C24.2, C25.2, COM1.5, COM2.5, COM3.5, COM4.5, D1.1 (K), D2.1 (K), D3.1 (K), D4.1 (K), D5.1 (K), D6.1 (K), H1.1, H2.1, H3.1, H4.1, J1.2, J4.5, J4.7, J5.2, J5.3, J6.4, J6.6, J6.8, J6.10, U1.14 (GND), U1.28 (GND), U1.45 (GND), U1.61 (GND), U2.8 (GND), U3.15 (GND), U4.15 (GND), U5.15 (GND), U6.15 (GND), U7.7 (GND), X1.4 (GND)
VCC: C1.1, C2.1, C3.1, C4.1, C5.1, C6.1, C7.1, C10.2, C13.2, C17.2, C21.2, C24.1, C25.1, J4.1, J4.3, J5.1, U1.4 (VCC), U1.21 (VCC), U1.35 (VCC), U1.52 (VCC), U2.16 (VCC), U3.16 (VCC), U4.16 (VCC), U5.16 (VCC), U6.16 (VCC), U7.14 (VCC), X1.8 (Vcc)
